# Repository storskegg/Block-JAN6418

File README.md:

# Block-JAN6418

A simple yet flexible gain stage based on the JAN6418 subminiature pentode.

## Features

- Filament supply options:
    - 2x resistor voltage drop
    - Optional bypass capacitor
- Pentode/Triode mode:
    - Triode: Jumper (0 Ohm resistor) S2 to the plate
    - Pentode: Solder a resistor between S2 and B+, and S2 and ground
    - Pentode: Solder leads to an off-board potentiometer in lieu of the two
      resistors
- Impedance controlled PCB stack-up:
    - Top, Inner-2, and Bottom copper fill ground planes
    - Signal lines on Inner-1 layer
    - Power lines on Bottom Layer
    - Vias along signal path for improved impedance control
- Mounting holes on either side of the tube for securing using rubber or
  silicone grommets, and a pair of 2.54mm (0.1in) zipties.

## Background

I've been designing a blues harp preamp for a buddy of mine, and it occurred to
me that all valve gain blocks are essentially the same, just with some variance
in component values. Because I tend to have different ideas for an individual
gain block, and different ideas about interstage connections (capacitor types,
tone stack, delay/echo, etc), having this board allows me to play with different
ideas more easily than pulling up components from the breadboard, but at the
cost of components soldered into place.

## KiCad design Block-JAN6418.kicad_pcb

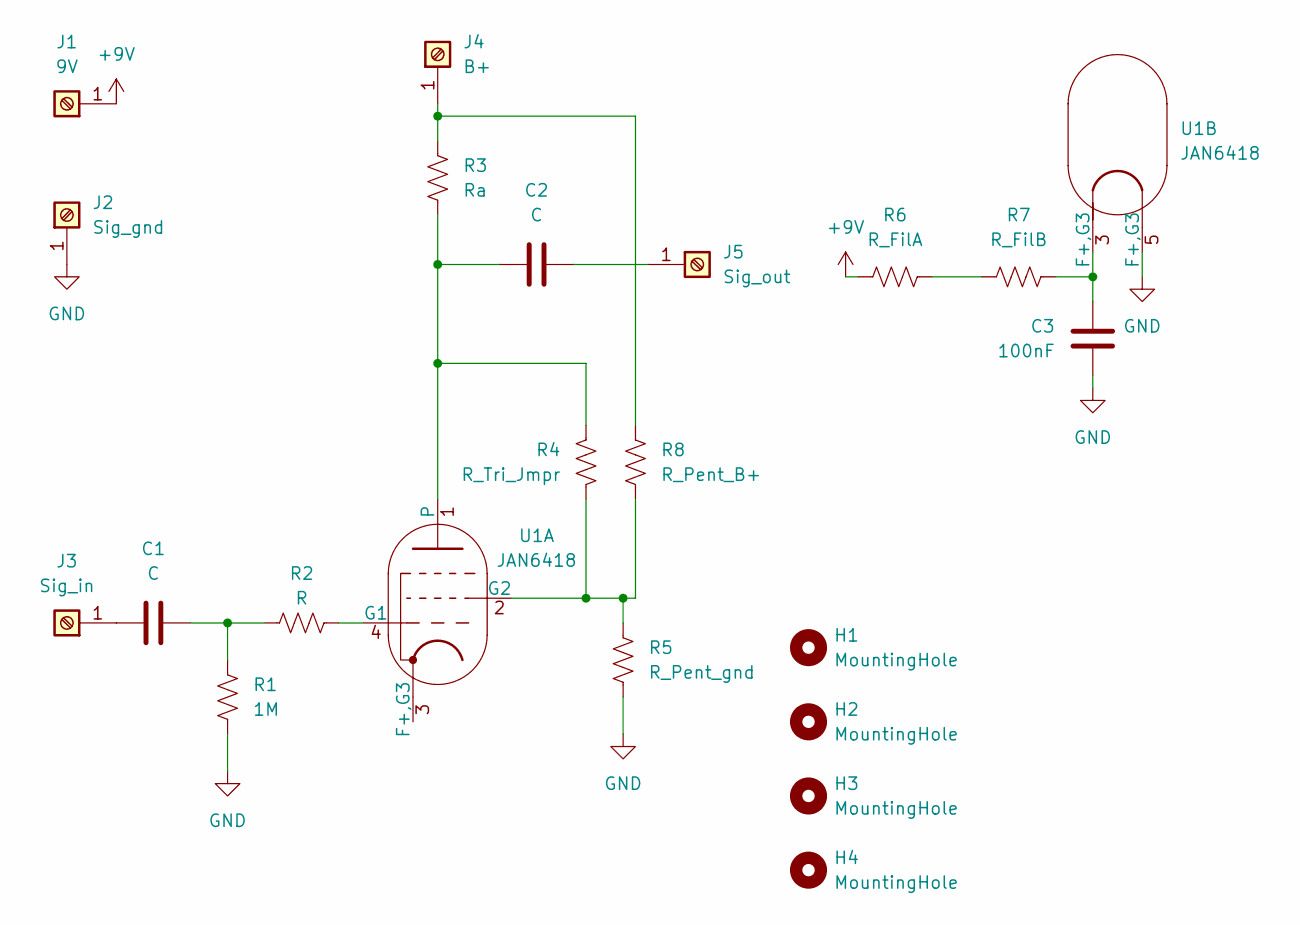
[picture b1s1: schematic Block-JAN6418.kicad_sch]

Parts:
C1, C2: C; C_Disc_D7.5mm_W2.5mm_P5.00mm
C3: 100nF; C_Rect_L4.6mm_W2.0mm_P2.50mm_MKS02_FKP02
H1, H2, H3, H4: MountingHole; MountingHole_2.2mm_M2
J1: 9V; TerminalBlock_MetzConnect_360271_1x01_Horizontal_ScrewM3.0_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
J2: Sig_gnd; TerminalBlock_MetzConnect_360271_1x01_Horizontal_ScrewM3.0_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
J3: Sig_in; TerminalBlock_MetzConnect_360271_1x01_Horizontal_ScrewM3.0_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
J4: B+; TerminalBlock_MetzConnect_360271_1x01_Horizontal_ScrewM3.0_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
J5: Sig_out; TerminalBlock_MetzConnect_360271_1x01_Horizontal_ScrewM3.0_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
R1: 1M; R_Axial_DIN0309_L9.0mm_D3.2mm_P12.70mm_Horizontal
R2: R; R_Axial_DIN0309_L9.0mm_D3.2mm_P12.70mm_Horizontal
R3: Ra; R_Axial_DIN0309_L9.0mm_D3.2mm_P12.70mm_Horizontal
R4: R_Tri_Jmpr; R_Axial_DIN0309_L9.0mm_D3.2mm_P2.54mm_Vertical
R5: R_Pent_gnd; R_Axial_DIN0309_L9.0mm_D3.2mm_P2.54mm_Vertical
R6: R_FilA; R_Axial_DIN0309_L9.0mm_D3.2mm_P2.54mm_Vertical
R7: R_FilB; R_Axial_DIN0309_L9.0mm_D3.2mm_P2.54mm_Vertical
R8: R_Pent_B+; R_Axial_DIN0309_L9.0mm_D3.2mm_P2.54mm_Vertical
U1: JAN6418; Valve_Mini_Pentode_Linear

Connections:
+9V: J1.1, R6.2
GND: C3.2, J2.1, R1.2, R5.2, U1.5 (F+,G3)
unnamed: C1.2, R1.1, R2.1
unnamed: C3.1, R7.2, U1.3 (F+,G3)
unnamed: C1.1, J3.1
unnamed: J4.1, R3.1, R8.1
unnamed: C2.2, J5.1
unnamed: R6.1, R7.1
unnamed: R2.2, U1.4 (G1)
unnamed: R4.2, R5.1, R8.2, U1.2 (G2)
unnamed: C2.1, R3.2, R4.1, U1.1

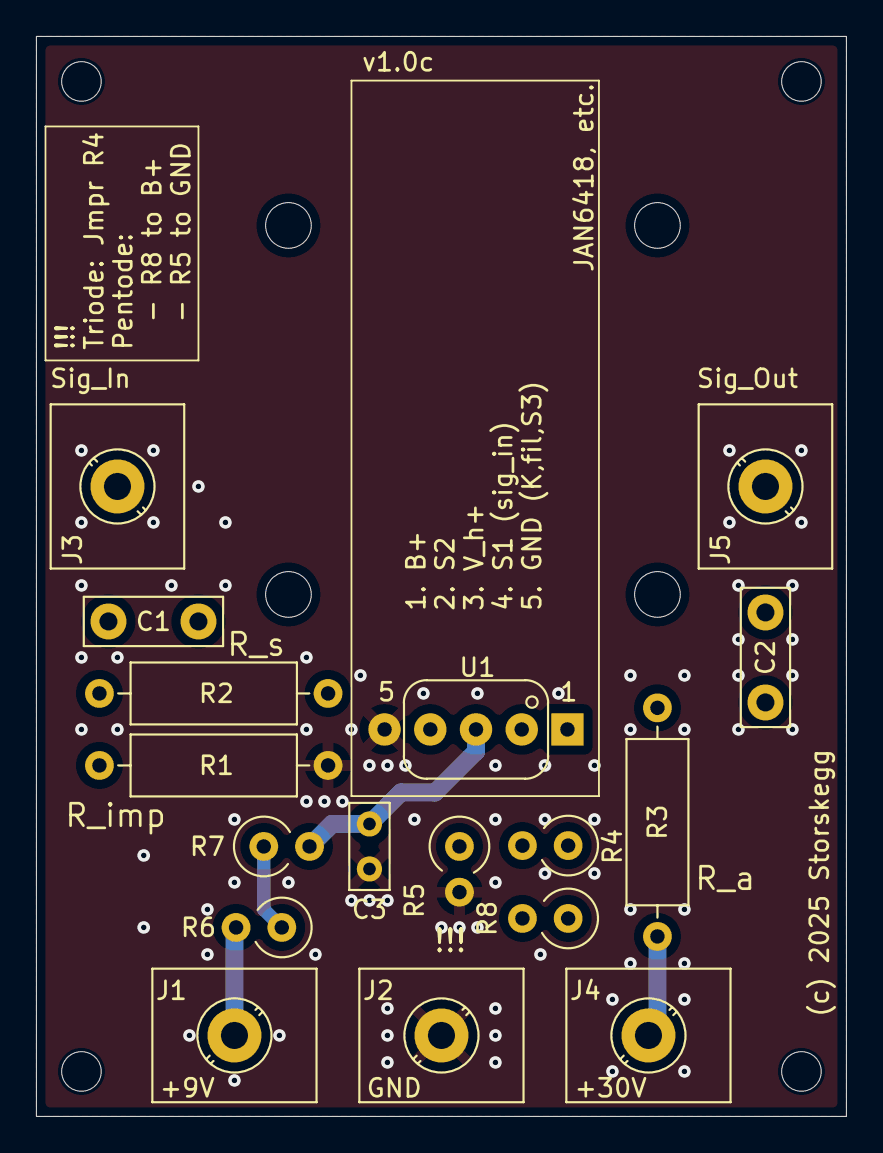
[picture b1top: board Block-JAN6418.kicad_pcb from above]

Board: 4 copper layers, 45.0 x 60.0 mm, 21 parts (0 on the bottom side), 11 nets.

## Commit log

2024-10-14 Add project files
2024-10-17 narrow the board, and add some additional silkscreening
2025-01-18 shrinkage
2025-01-19 bigger change...
    1. Added L1 Ground Plane
    2. Added filter and bandpass capacitors to LM317L optional block
    3. `Sig_in` and `Sig_gnd` swapped physical locations...
    1. `Sig_gnd` is now closer to PSU block ground connections (lower
    impedance ground paths)
    2. `Sig_gnd` now closer to `R_impedance` ground connection
2025-01-19 lower impedance of sig_gnd connection
2025-01-19 update sch from pcb, gen gerbers, drl files
2025-01-19 generate drl, grbrs, update sch from pcb
2025-01-20 add JLCPCB design rules
2025-01-22 abide JLCPCB rules
2025-02-26 v1.0b Re-routing
    - Added ground fill to L2, respective vias
    - Re-routed power rail solder points to the bottom of the board so that
    power can be jumpered up from the enclosure front board (will house
    power bars, I/O, pots, etc)
2025-03-07 tighten up some alignments
2025-03-07 add drill maps (dxf)

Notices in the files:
Block-JAN6418.kicad_pcb:
(c) 2025 Storskegg
